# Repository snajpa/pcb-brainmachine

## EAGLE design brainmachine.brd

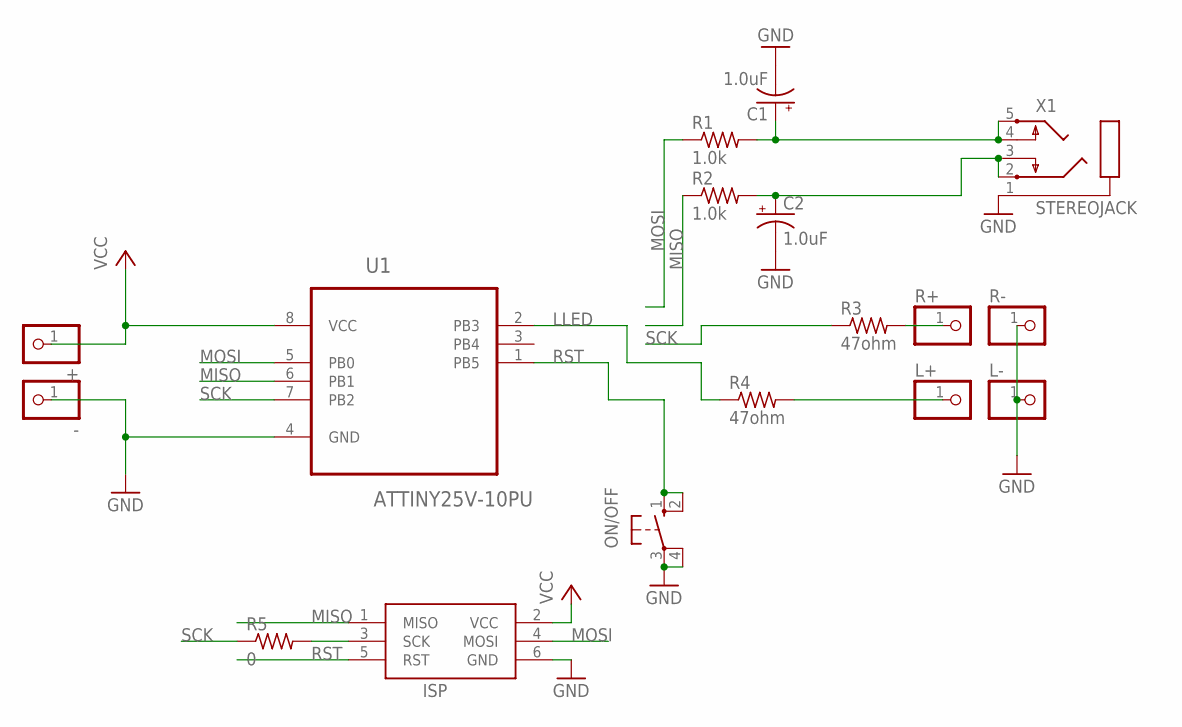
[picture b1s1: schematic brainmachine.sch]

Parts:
+: PINHD-1X1; 1X01
-: PINHD-1X1; 1X01
C1, C2: 1.0uF; E2,5-5
ISP: AVRISP-6; AVRISP
L+: PINHD-1X1; 1X01
L-: PINHD-1X1; 1X01
ON/OFF: 10-XX; B3F-10XX
R1, R2: 1.0k; 0207/10
R3, R4: 47ohm; 0207/10
R5: 0; 0207/10
R+: PINHD-1X1; 1X01
R-: PINHD-1X1; 1X01
U1: ATTINY25V-10PU; DIP254P762X533-8
X1: STEREOJACK; STX3100

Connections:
GND: -.1, C1.-, C2.-, ISP.6 (GND), L-.1, ON/OFF.3, ON/OFF.4 (P1), R-.1, U1.4 (GND), X1.1
LEYE+: L+.1, R4.2
LLED: R4.1, U1.2 (PB3)
MISO: ISP.1 (MISO), R2.1, U1.6 (PB1)
MOSI: ISP.4 (MOSI), R1.1, U1.5 (PB0)
unnamed: C1.+, R1.2, X1.4, X1.5
unnamed: ISP.3 (SCK), R5.2
unnamed: C2.+, R2.2, X1.2, X1.3
unnamed: R3.2, R+.1
RST: ISP.5 (RST), ON/OFF.1 (S), ON/OFF.2 (S1), U1.1 (PB5)
SCK: R3.1, R5.1, U1.7 (PB2)
VCC: +.1, ISP.2 (VCC), U1.8 (VCC)

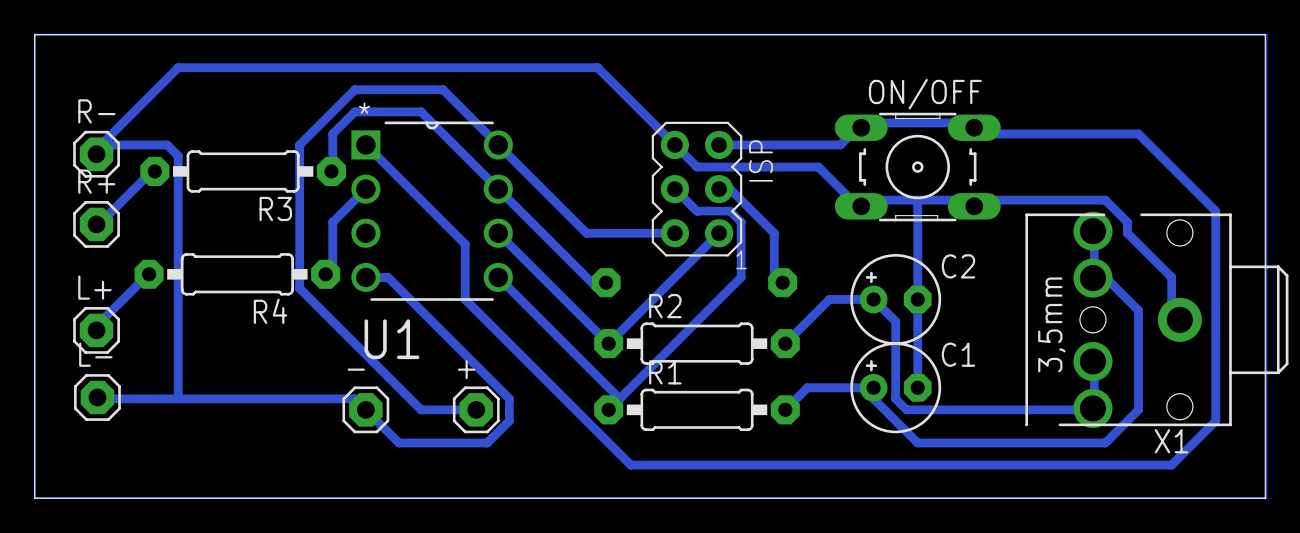
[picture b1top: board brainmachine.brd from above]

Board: 2 copper layers, 70.8 x 26.7 mm, 17 parts (1 on the bottom side), 12 nets.

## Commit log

2016-05-15 add files
